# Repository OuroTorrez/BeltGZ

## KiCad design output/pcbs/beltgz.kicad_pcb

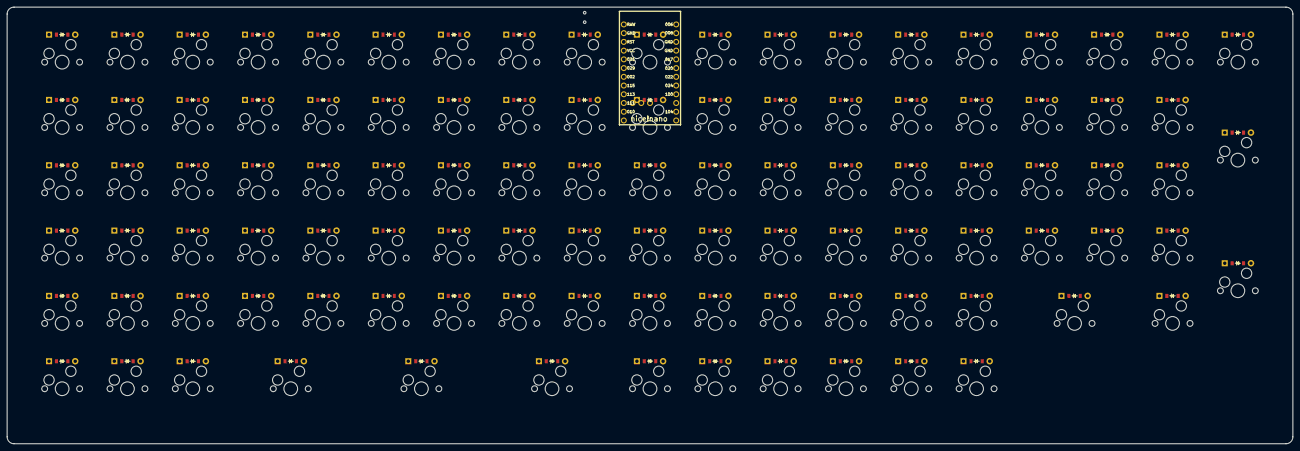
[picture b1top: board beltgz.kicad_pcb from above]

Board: 2 copper layers, 374.0 x 127.0 mm, 210 parts (0 on the bottom side), 107 nets, no tracks yet.

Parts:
B1: Panasonic_EVQPUL_EVQPUC
D1, D2, D3, D4, D5, D6, D7, D8, D9, D10, D11, D12, D13, D14, D15, D16, D17, D18, D19, D20, D21, D22, D23, D24, D25, D26, D27, D28, D29, D30, D31, D32, D33, D34, D35, D36, D37, D38, D39, D40, D41, D42, D43, D44, D45, D46, D47, D48, D49, D50, D51, D52, D53, D54, D55, D56, D57, D58, D59, D60, D61, D62, D63, D64, D65, D66, D67, D68, D69, D70, D71, D72, D73, D74, D75, D76, D77, D78, D79, D80, D81, D82, D83, D84, D85, D86, D87, D88, D89, D90, D91, D92, D93, D94, D95, D96, D97, D98, D99, D100, D101, D102, D103, D104: ComboDiode
MCU1: nice_nano
S1, S2, S3, S4, S5, S6, S7, S8, S9, S10, S11, S12, S13, S14, S15, S16, S17, S18, S19, S20, S21, S22, S23, S24, S25, S26, S27, S28, S29, S30, S31, S32, S33, S34, S35, S36, S37, S38, S39, S40, S41, S42, S43, S44, S45, S46, S47, S48, S49, S50, S51, S52, S53, S54, S55, S56, S57, S58, S59, S60, S61, S62, S63, S64, S65, S66, S67, S68, S69, S70, S71, S72, S73, S74, S75, S76, S77, S78, S79, S80, S81, S82, S83, S84, S85, S86, S87, S88, S89, S90, S91, S92, S93, S94, S95, S96, S97, S98, S99, S100, S101, S102, S103, S104: MX

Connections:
GND: B1.1, MCU1.3, MCU1.4, MCU1.23
P: D1.1, D7.1, D13.1, D49.1, D55.1, D61.1, D67.1, D73.1, D79.1
RST: B1.2, MCU1.22
backspace_default: D99.2, S99.2
bloqd_esc: D92.2, S92.2
bloqd_mayus: D89.2, S89.2
bloqd_symbol: D91.2, S91.2
bloqd_tab: D90.2, S90.2
cero_default: D102.2, S102.2
enter_default: D101.2, S101.2
esc_ctrl: D1.2, S1.2
esc_esc: D6.2, S6.2
esc_mayus: D3.2, S3.2
esc_shift: D2.2, S2.2
esc_symbol: D5.2, S5.2
esc_tab: D4.2, S4.2
f1_ctrl: D7.2, S7.2
f1_esc: D12.2, S12.2
f1_mayus: D9.2, S9.2
f1_shift: D8.2, S8.2
f1_symbol: D11.2, S11.2
f1_tab: D10.2, S10.2
f2_ctrl: D13.2, S13.2
f2_esc: D18.2, S18.2
f2_mayus: D15.2, S15.2
f2_shift: D14.2, S14.2
f2_symbol: D17.2, S17.2
f2_tab: D16.2, S16.2
f3_esc: D23.2, S23.2
f3_mayus: D20.2, S20.2
f3_shift: D19.2, S19.2
f3_symbol: D22.2, S22.2
f3_tab: D21.2, S21.2
f4_esc: D28.2, S28.2
f4_mayus: D25.2, S25.2
f4_shift: D24.2, S24.2
f4_symbol: D27.2, S27.2
f4_tab: D26.2, S26.2
f5_esc: D33.2, S33.2
f5_mayus: D30.2, S30.2
f5_shift: D29.2, S29.2
f5_symbol: D32.2, S32.2
f5_tab: D31.2, S31.2
f6_esc: D38.2, S38.2
f6_mayus: D35.2, S35.2
f6_shift: D34.2, S34.2
f6_symbol: D37.2, S37.2
f6_tab: D36.2, S36.2
f7_esc: D43.2, S43.2
f7_mayus: D40.2, S40.2
f7_shift: D39.2, S39.2
f7_symbol: D42.2, S42.2
f7_tab: D41.2, S41.2
f8_esc: D48.2, S48.2
f8_mayus: D45.2, S45.2
f8_shift: D44.2, S44.2
f8_symbol: D47.2, S47.2
f8_tab: D46.2, S46.2
f9_ctrl: D49.2, S49.2
f9_esc: D54.2, S54.2
f9_mayus: D51.2, S51.2
f9_shift: D50.2, S50.2
f9_symbol: D53.2, S53.2
f9_tab: D52.2, S52.2
f10_ctrl: D55.2, S55.2
f10_esc: D60.2, S60.2
f10_mayus: D57.2, S57.2
f10_shift: D56.2, S56.2
f10_symbol: D59.2, S59.2
f10_tab: D58.2, S58.2
f11_ctrl: D61.2, S61.2
f11_esc: D66.2, S66.2
f11_mayus: D63.2, S63.2
f11_shift: D62.2, S62.2
f11_symbol: D65.2, S65.2
f11_tab: D64.2, S64.2
f12_ctrl: D67.2, S67.2
f12_esc: D72.2, S72.2
f12_mayus: D69.2, S69.2
f12_shift: D68.2, S68.2
f12_symbol: D71.2, S71.2
f12_tab: D70.2, S70.2
inser_esc: D88.2, S88.2
inser_mayus: D85.2, S85.2
inser_symbol: D87.2, S87.2
inser_tab: D86.2, S86.2
intro_default: D104.2, S104.2
knob_esc: D98.2, S98.2
pant_ctrl: D79.2, S79.2
pant_esc: D84.2, S84.2
pant_mayus: D81.2, S81.2
pant_shift: D80.2, S80.2
pant_symbol: D83.2, S83.2
pant_tab: D82.2, S82.2
pausa_esc: D97.2, S97.2
pausa_mayus: D94.2, S94.2
pausa_shift: D93.2, S93.2
pausa_symbol: D96.2, S96.2
pausa_tab: D95.2, S95.2
plus_default: D103.2, S103.2
space_default: D100.2, S100.2
supr_ctrl: D73.2, S73.2
supr_esc: D78.2, S78.2
supr_mayus: D75.2, S75.2
supr_shift: D74.2, S74.2
supr_symbol: D77.2, S77.2
supr_tab: D76.2, S76.2

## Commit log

2024-08-30 Inicializa proyecto en creación de PCB
2024-08-30 Reset button
2024-09-03 nRF5340
2024-09-03 arduino nano
2024-09-05 nada, creo
2024-09-05 comentario
2024-09-06 hice un desmadre con los spacing
2024-09-09 mill-max pcb ready
2024-09-24 nada
2025-07-02 ignore
